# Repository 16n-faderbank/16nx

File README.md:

# 16nx: ECAD files

Electronics CAD and design for the 16nx faderbank, in KiCAD 8.0.4 format.

## Revision

Board revision C

## Design Notes

16nx is a redesign of the original [16n][16n] project. It has identical functionality to the original project. The changes are:

- replace Teensy 3.2 board with RP2040 microcontroller and supporting circuitry, directly on the board
- move to USB-C connector
- add more power filtering onto 5V line
- redesign analog circuitry for CV outs. Rather than running the faders at 5V and dividing down to ~3.2V for the microcontroller, 16nx runs at 3.3V everywhere, and amplifies fader values _up_ to ~5V via the MCP6004 opamps.
- move to vertical Thonkiconn jacks for CV outputs (cheaper, easier to access, easier to purchase)
- move to new horizontal jack parts for MIDI/I2C, ensuring there are no connectors on front panel (4332.2330 Schurter jacks)
- assume all SMT will be machine-placed; passives are now down to 0402, various QFN/USON parts that should be reflowed.

The only manual assembly anticipated on the board is of the through-hole components: faders, jacks, switch. Everything else is expected to be assembled via a PCBA house. The product is designed around relatively generic, off-the-shelf parts available at eg [JLC][jlc].

Gerbers are not committed to the repository; they will be supplied as part of releases.

## BOM

Bom is in `16nx-bom.csv`. It contains descriptions of parts and part numbers either at JLC or at Mouser, which is how the author built his boards. Thonkiconn are available from [Thonk][thonk].

In general, most of the passives requirements are not fussy: 1% resistors and capacitors with suitable voltage tolerance will be fine. The crystal and its capacitors are quite specifically chosen, as is the Winbond flash RAM.

The Alps faders are available in a number of resistances; the actual resistance of the fader doesn't matter, it's just being used as a voltage divider; if you can't get 10k but _can_ get 20k faders, that's fine. They **must** be linear taper, however. Do not use log/audio taper faders; you _cannot_ fix that in software. (Yes, people have asked.)

## Debug connector

The debug connector on the front of the board is a JST-SH connector breaking out ARM SWD (single-wire-debug) ready for connection to a [Pico Debug Probe][debugprobe]. This allows developers to use open-source debug tools (OpenOCD, [Cortex Debug](https://github.com/Marus/cortex-debug)) to debug the firmware in a more... pleasant manner than endless serial dumps.

## I2C pullups

Two 4.7kohm pullups are available for the I2C lines. To engage them, join the two solder jumpers at the top left of the board with a blob of solder. (You may not need these if you already have suitable pull-up impedance on your I2C lines).

## Pinouts

| GPIO | Description        |
| ---- | ------------------ |
| 2    | On board LED       |
| 4    | UART TX (MIDI OUT) |
| 10   | SDA (I2C1)         |
| 11   | SCL (I2C1)         |
| 18   | S0                 |
| 19   | S1                 |
| 20   | S2                 |
| 21   | S3                 |
| 26   | ADC0               |

## Front panels

Alongside the usual KiCAD files, this directory also includes a `panels` directory containing DXF files for top/bottom panels, and a mechanical drawing of the top panel. A schematic in PDF format is also included.

## Licensing

As per the `LICENSE.md` file, the 16nx hardware is licensed as **[Creative Commons Attribution-Share-Alike 4.0][ccsa]**.

---

[octobom]: https://octopart.com/bom-tool/unJxkzvR
[16n]: https://github.com/16n-faderbank/16n/tree/main/electronics
[jlc]: https://jlcpcb.com/
[ccsa]: https://creativecommons.org/licenses/by-sa/4.0/legalcode
[thonk]: https://thonk.co.uk/

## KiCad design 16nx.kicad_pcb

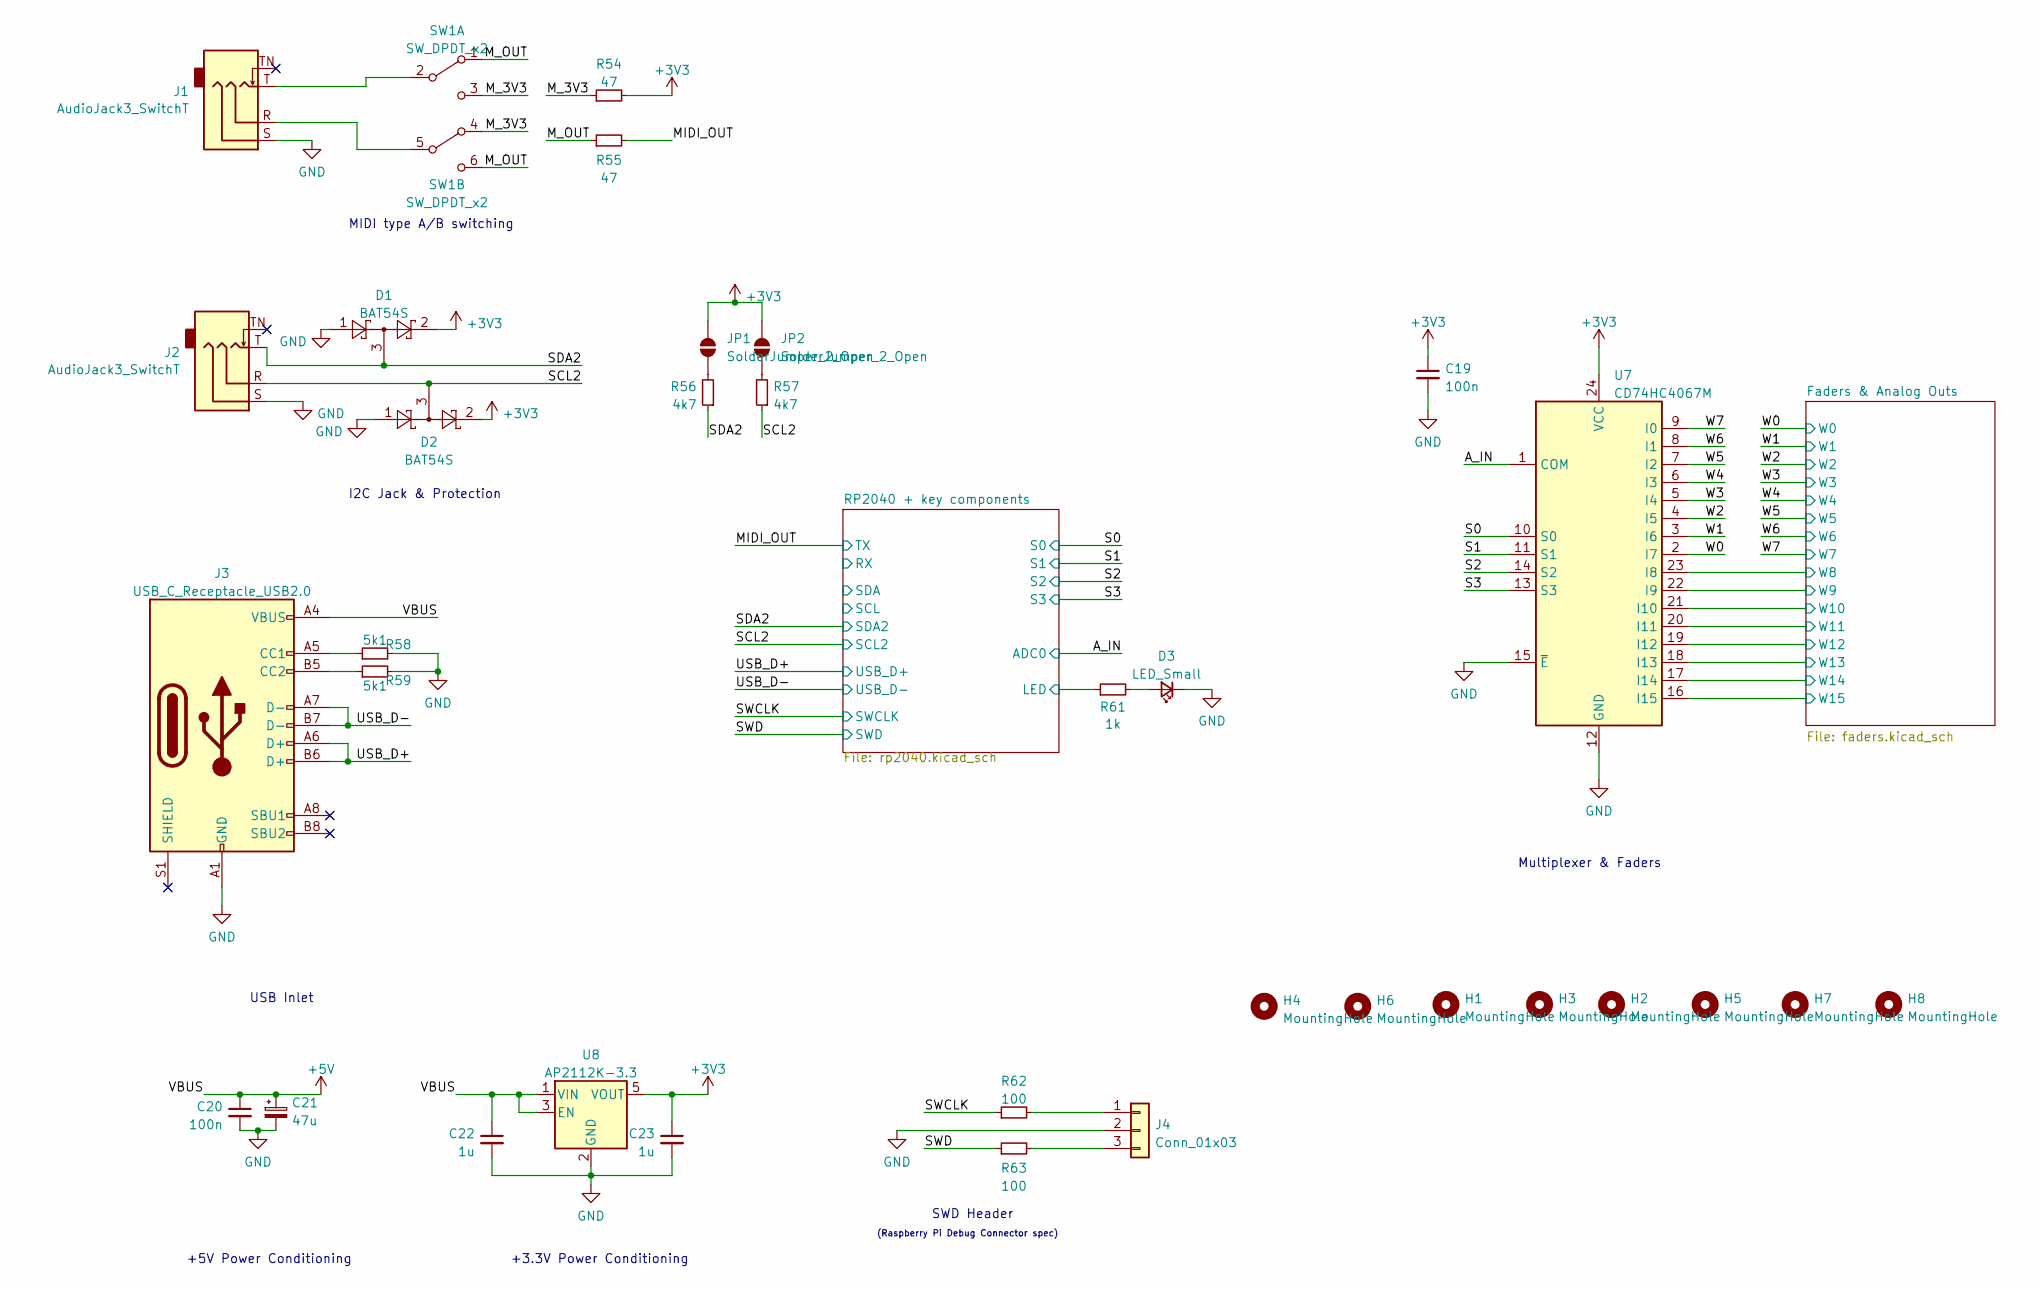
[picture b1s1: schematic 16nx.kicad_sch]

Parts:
C19, C20: 100n; C_0402_1005Metric
C21: 47u; CP_Elec_5x5.4
C22, C23: 1u; C_0402_1005Metric
D1, D2: BAT54S; SOT-23
D3: LED_Small; LED_0805_2012Metric_Pad1.15x1.40mm_HandSolder
H1, H2, H3, H4, H5, H6, H7, H8: MountingHole; MountingHole_2.7mm_M2.5
J1, J2: AudioJack3_SwitchT; Schurter 4832.2330
J3: USB_C_Receptacle_USB2.0; USB_C_Receptacle_HRO_TYPE-C-31-M-12
J4: Conn_01x03; JST_SM03B-SRSS-TB(LF)(SN)
JP1, JP2: SolderJumper_2_Open; SolderJumper-2_P1.3mm_Open_RoundedPad1.0x1.5mm
R54, R55: 47; R_0402_1005Metric
R56, R57: 4k7; R_0402_1005Metric
R58, R59: 5k1; R_0402_1005Metric
R61: 1k; R_0402_1005Metric
R62, R63: 100; R_0402_1005Metric
SW1: SW_DPDT_x2; SW_E-Switch_EG2211_DPDT
U7: CD74HC4067M; SSOP-24_5.3x8.2mm_P0.65mm
U8: AP2112K-3.3; SOT-23-5

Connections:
+3V3: C19.1, C23.1, D1.2, D2.2, JP1.2 (B), JP2.2 (B), R54.2, U7.24 (VCC), U8.5 (VOUT); also elsewhere on the board
+5V: C20.1, C21.1, C22.1, J3.A4 (VBUS), J3.A9 (VBUS), J3.B4 (VBUS), J3.B9 (VBUS), U8.1 (VIN), U8.3 (EN); also elsewhere on the board
/A_IN: U7.1 (COM); also elsewhere on the board
/Faders & Analog Outs/W8: U7.23 (I8); also elsewhere on the board
/Faders & Analog Outs/W9: U7.22 (I9); also elsewhere on the board
/Faders & Analog Outs/W10: U7.21 (I10); also elsewhere on the board
/Faders & Analog Outs/W11: U7.20 (I11); also elsewhere on the board
/Faders & Analog Outs/W12: U7.19 (I12); also elsewhere on the board
/Faders & Analog Outs/W13: U7.18 (I13); also elsewhere on the board
/Faders & Analog Outs/W14: U7.17 (I14); also elsewhere on the board
/Faders & Analog Outs/W15: U7.16 (I15); also elsewhere on the board
/MIDI_OUT: R55.2; also elsewhere on the board
/M_3V3: R54.1, SW1.3 (C), SW1.4 (A)
/M_OUT: R55.1, SW1.1 (A), SW1.6 (C)
/RP2040 + key components/LED: R61.1; also elsewhere on the board
/S0: U7.10 (S0); also elsewhere on the board
/S1: U7.11 (S1); also elsewhere on the board
/S2: U7.14 (S2); also elsewhere on the board
/S3: U7.13 (S3); also elsewhere on the board
/SCL2: D2.3, J2.R, R57.1; also elsewhere on the board
/SDA2: D1.3, J2.T, R56.1; also elsewhere on the board
/SWCLK: R62.1; also elsewhere on the board
/SWD: R63.1; also elsewhere on the board
/USB_D+: J3.A6 (D+), J3.B6 (D+); also elsewhere on the board
/USB_D-: J3.A7 (D-), J3.B7 (D-); also elsewhere on the board
/W0: U7.2 (I7); also elsewhere on the board
/W1: U7.3 (I6); also elsewhere on the board
/W2: U7.4 (I5); also elsewhere on the board
/W3: U7.5 (I4); also elsewhere on the board
/W4: U7.6 (I3); also elsewhere on the board
/W5: U7.7 (I2); also elsewhere on the board
/W6: U7.8 (I1); also elsewhere on the board
/W7: U7.9 (I0); also elsewhere on the board
GND: C19.2, C20.2, C21.2, C22.2, C23.2, D1.1, D2.1, D3.1 (K), J1.S, J2.S, J3.A1 (GND), J3.A12 (GND), J3.B1 (GND), J3.B12 (GND), J4.2, R58.2, R59.2, U7.12 (GND), U7.15 (~E), U8.2 (GND); also elsewhere on the board
unnamed: D3.2 (A), R61.2
unnamed: J3.A5 (CC1), R58.1
unnamed: J3.B5 (CC2), R59.1
unnamed: J4.1, R62.2
unnamed: J4.3, R63.2
unnamed: JP1.1 (A), R56.2
unnamed: JP2.1 (A), R57.2
unnamed: J1.T, SW1.2 (B)
unnamed: J1.R, SW1.5 (B)

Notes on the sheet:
USB Inlet
+5V Power Conditioning
I2C Jack & Protection
SWD Header
+3.3V Power Conditioning
MIDI type A/B switching
(Raspberry Pi Debug Connector spec)
Multiplexer & Faders

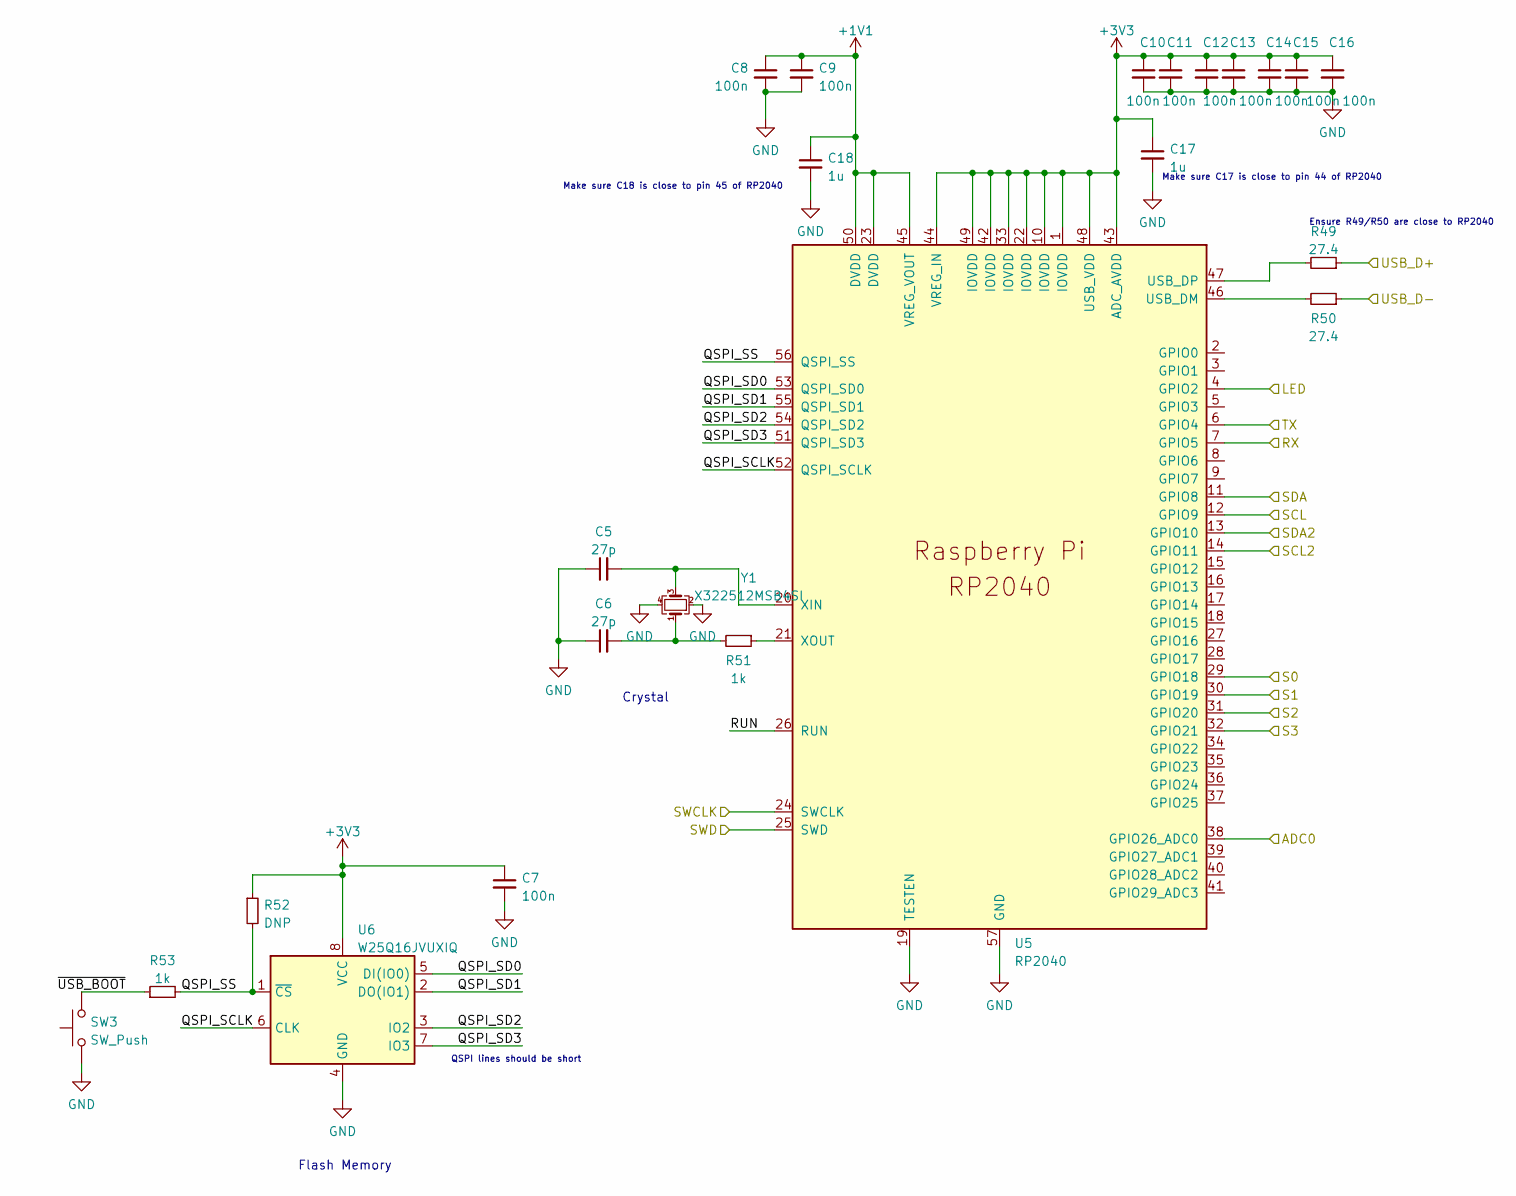
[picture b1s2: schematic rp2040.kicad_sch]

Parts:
C5, C6: 27p; C_0402_1005Metric
C7, C8, C9, C10, C11, C12, C13, C14, C15, C16: 100n; C_0402_1005Metric
C17, C18: 1u; C_0402_1005Metric
R49, R50: 27.4; R_0402_1005Metric
R51, R53: 1k; R_0402_1005Metric
R52: DNP; R_0402_1005Metric
SW3: SW_Push; SW_SPST_EVQP2
U5: RP2040; RP2040-QFN-56
U6: W25Q16JVUXIQ; USON-8_L3.0-W2.0-P0.50-BL-EP
Y1: X322512MSB4SI; Crystal_SMD_3225-4Pin_3.2x2.5mm

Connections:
+1V1: C8.1, C9.1, C18.1, U5.23 (DVDD), U5.45 (VREG_VOUT), U5.50 (DVDD)
+3V3: C7.1, C10.1, C11.1, C12.1, C13.1, C14.1, C15.1, C16.1, C17.1, R52.1, U5.1 (IOVDD), U5.10 (IOVDD), U5.22 (IOVDD), U5.33 (IOVDD), U5.42 (IOVDD), U5.43 (ADC_AVDD), U5.44 (VREG_IN), U5.48 (USB_VDD), U5.49 (IOVDD), U6.8 (VCC); also elsewhere on the board
/A_IN: U5.38 (GPIO26_ADC0); also elsewhere on the board
/MIDI_OUT: U5.6 (GPIO4); also elsewhere on the board
/RP2040 + key components/LED: U5.4 (GPIO2); also elsewhere on the board
/RP2040 + key components/QSPI_SCLK: U5.52 (QSPI_SCLK), U6.6 (CLK)
/RP2040 + key components/QSPI_SD0: U5.53 (QSPI_SD0), U6.5 (DI(IO0))
/RP2040 + key components/QSPI_SD1: U5.55 (QSPI_SD1), U6.2 (DO(IO1))
/RP2040 + key components/QSPI_SD2: U5.54 (QSPI_SD2), U6.3 (IO2)
/RP2040 + key components/QSPI_SD3: U5.51 (QSPI_SD3), U6.7 (IO3)
/RP2040 + key components/QSPI_SS: R52.2, R53.2, U5.56 (QSPI_SS), U6.1 (~CS)
/RP2040 + key components/RUN: U5.26 (RUN)
/RP2040 + key components/RX: U5.7 (GPIO5)
/RP2040 + key components/SCL: U5.12 (GPIO9)
/RP2040 + key components/SDA: U5.11 (GPIO8)
/RP2040 + key components/~USB_BOOT: R53.1, SW3.2
/S0: U5.29 (GPIO18); also elsewhere on the board
/S1: U5.30 (GPIO19); also elsewhere on the board
/S2: U5.31 (GPIO20); also elsewhere on the board
/S3: U5.32 (GPIO21); also elsewhere on the board
/SCL2: U5.14 (GPIO11); also elsewhere on the board
/SDA2: U5.13 (GPIO10); also elsewhere on the board
/SWCLK: U5.24 (SWCLK); also elsewhere on the board
/SWD: U5.25 (SWD); also elsewhere on the board
/USB_D+: R49.1; also elsewhere on the board
/USB_D-: R50.1; also elsewhere on the board
GND: C5.1, C6.1, C7.2, C8.2, C9.2, C10.2, C11.2, C12.2, C13.2, C14.2, C15.2, C16.2, C17.2, C18.2, SW3.1, U5.19 (TESTEN), U5.57 (GND), U6.4 (GND), Y1.2, Y1.4; also elsewhere on the board
unnamed: C6.2, R51.2, Y1.1
unnamed: R50.2, U5.46 (USB_DM)
unnamed: R49.2, U5.47 (USB_DP)
unnamed: C5.2, U5.20 (XIN), Y1.3
unnamed: R51.1, U5.21 (XOUT)

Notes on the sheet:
Crystal
Ensure R49/R50 are close to RP2040
Make sure C17 is close to pin 44 of RP2040
Flash Memory
QSPI lines should be short
Make sure C18 is close to pin 45 of RP2040

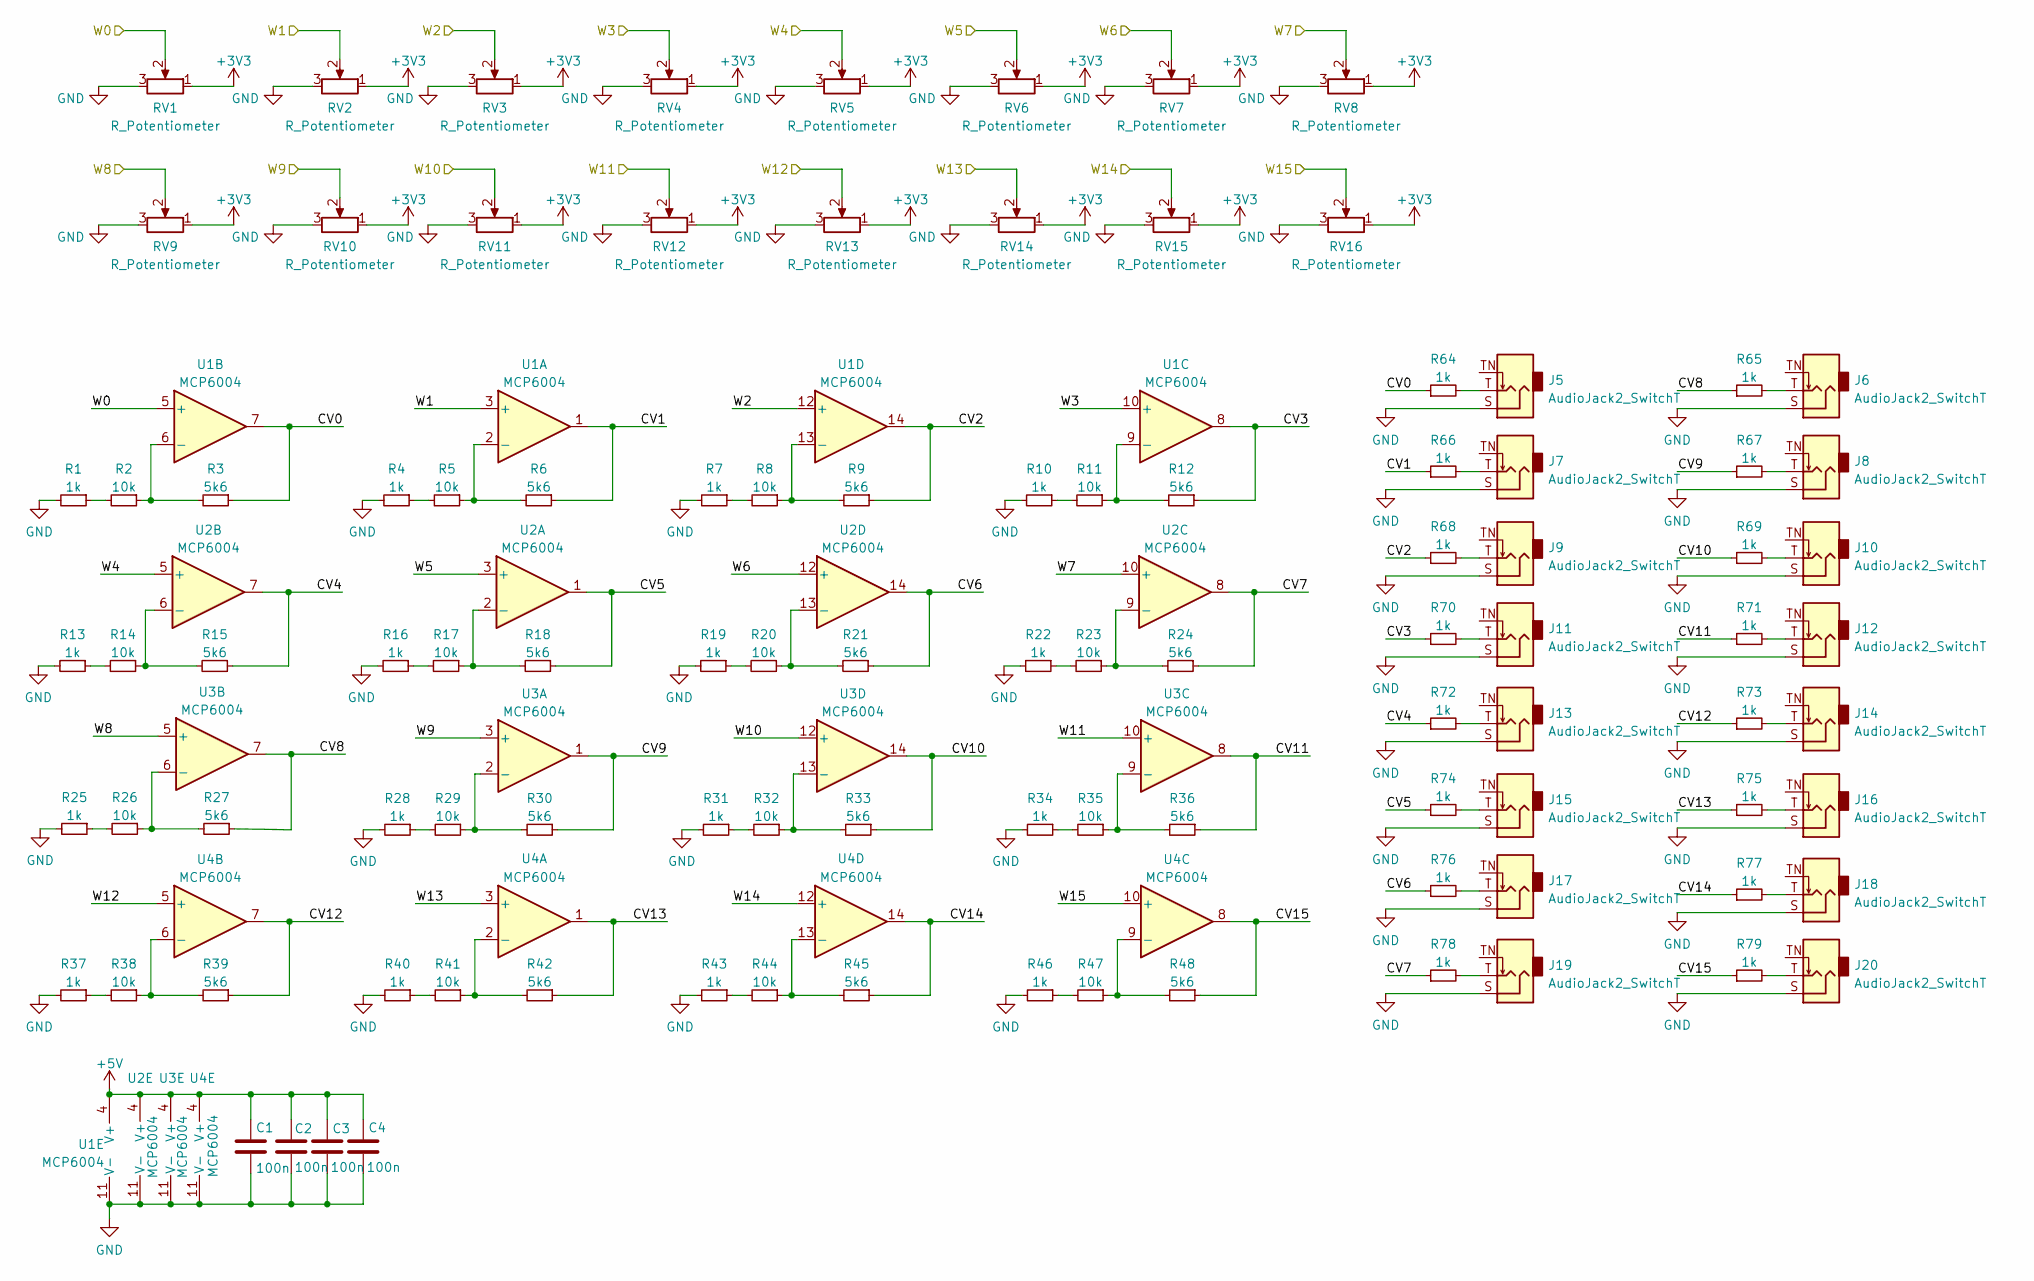
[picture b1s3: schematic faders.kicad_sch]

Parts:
C1, C2, C3, C4: 100n; C_0402_1005Metric
J5, J6, J7, J8, J9, J10, J11, J12, J13, J14, J15, J16, J17, J18, J19, J20: AudioJack2_SwitchT; Thonkiconn
R1, R4, R7, R10, R13, R16, R19, R22, R25, R28, R31, R34, R37, R40, R43, R46, R64, R65, R66, R67, R68, R69, R70, R71, R72, R73, R74, R75, R76, R77, R78, R79: 1k; R_0402_1005Metric
R2, R5, R8, R11, R14, R17, R20, R23, R26, R29, R32, R35, R38, R41, R44, R47: 10k; R_0402_1005Metric
R3, R6, R9, R12, R15, R18, R21, R24, R27, R30, R33, R36, R39, R42, R45, R48: 5k6; R_0402_1005Metric
RV1, RV2, RV3, RV4, RV5, RV6, RV7, RV8, RV9, RV10, RV11, RV12, RV13, RV14, RV15, RV16: R_Potentiometer; Alps_60mm_Fader
U1, U2, U3, U4: MCP6004; SOIC-14_3.9x8.7mm_P1.27mm

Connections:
+3V3: RV1.1, RV2.1, RV3.1, RV4.1, RV5.1, RV6.1, RV7.1, RV8.1, RV9.1, RV10.1, RV11.1, RV12.1, RV13.1, RV14.1, RV15.1, RV16.1; also elsewhere on the board
+5V: C1.1, C2.1, C3.1, C4.1, U1.4 (V+), U2.4 (V+), U3.4 (V+), U4.4 (V+); also elsewhere on the board
/Faders & Analog Outs/CV0: R3.1, R64.1, U1.7
/Faders & Analog Outs/CV1: R6.1, R66.1, U1.1
/Faders & Analog Outs/CV2: R9.1, R68.1, U1.14
/Faders & Analog Outs/CV3: R12.1, R70.1, U1.8
/Faders & Analog Outs/CV4: R15.1, R72.1, U2.7
/Faders & Analog Outs/CV5: R18.1, R74.1, U2.1
/Faders & Analog Outs/CV6: R21.1, R76.1, U2.14
/Faders & Analog Outs/CV7: R24.1, R78.1, U2.8
/Faders & Analog Outs/CV8: R27.1, R65.1, U3.7
/Faders & Analog Outs/CV9: R30.1, R67.1, U3.1
/Faders & Analog Outs/CV10: R33.1, R69.1, U3.14
/Faders & Analog Outs/CV11: R36.1, R71.1, U3.8
/Faders & Analog Outs/CV12: R39.1, R73.1, U4.7
/Faders & Analog Outs/CV13: R42.1, R75.1, U4.1
/Faders & Analog Outs/CV14: R45.1, R77.1, U4.14
/Faders & Analog Outs/CV15: R48.1, R79.1, U4.8
/Faders & Analog Outs/W8: RV9.2, U3.5 (+); also elsewhere on the board
/Faders & Analog Outs/W9: RV10.2, U3.3 (+); also elsewhere on the board
/Faders & Analog Outs/W10: RV11.2, U3.12 (+); also elsewhere on the board
/Faders & Analog Outs/W11: RV12.2, U3.10 (+); also elsewhere on the board
/Faders & Analog Outs/W12: RV13.2, U4.5 (+); also elsewhere on the board
/Faders & Analog Outs/W13: RV14.2, U4.3 (+); also elsewhere on the board
/Faders & Analog Outs/W14: RV15.2, U4.12 (+); also elsewhere on the board
/Faders & Analog Outs/W15: RV16.2, U4.10 (+); also elsewhere on the board
/W0: RV1.2, U1.5 (+); also elsewhere on the board
/W1: RV2.2, U1.3 (+); also elsewhere on the board
/W2: RV3.2, U1.12 (+); also elsewhere on the board
/W3: RV4.2, U1.10 (+); also elsewhere on the board
/W4: RV5.2, U2.5 (+); also elsewhere on the board
/W5: RV6.2, U2.3 (+); also elsewhere on the board
/W6: RV7.2, U2.12 (+); also elsewhere on the board
/W7: RV8.2, U2.10 (+); also elsewhere on the board
GND: C1.2, C2.2, C3.2, C4.2, J5.S, J6.S, J7.S, J8.S, J9.S, J10.S, J11.S, J12.S, J13.S, J14.S, J15.S, J16.S, J17.S, J18.S, J19.S, J20.S, R1.2, R4.2, R7.2, R10.2, R13.2, R16.2, R19.2, R22.2, R25.2, R28.2, R31.2, R34.2, R37.2, R40.2, R43.2, R46.2, RV1.3, RV2.3, RV3.3, RV4.3, RV5.3, RV6.3, RV7.3, RV8.3, RV9.3, RV10.3, RV11.3, RV12.3, RV13.3, RV14.3, RV15.3, RV16.3, U1.11 (V-), U2.11 (V-), U3.11 (V-), U4.11 (V-); also elsewhere on the board
unnamed: J5.T, R64.2
unnamed: J6.T, R65.2
unnamed: J7.T, R66.2
unnamed: J8.T, R67.2
unnamed: J9.T, R68.2
unnamed: J10.T, R69.2
unnamed: J11.T, R70.2
unnamed: J12.T, R71.2
unnamed: J13.T, R72.2
unnamed: J14.T, R73.2
unnamed: J15.T, R74.2
unnamed: J16.T, R75.2
unnamed: J17.T, R76.2
unnamed: J18.T, R77.2
unnamed: J19.T, R78.2
unnamed: J20.T, R79.2
unnamed: R1.1, R2.2
unnamed: R4.1, R5.2
unnamed: R7.1, R8.2
unnamed: R10.1, R11.2
unnamed: R13.1, R14.2
unnamed: R16.1, R17.2
unnamed: R19.1, R20.2
unnamed: R22.1, R23.2
unnamed: R25.1, R26.2
unnamed: R28.1, R29.2
unnamed: R31.1, R32.2
unnamed: R34.1, R35.2
unnamed: R37.1, R38.2
unnamed: R40.1, R41.2
unnamed: R43.1, R44.2
unnamed: R46.1, R47.2
unnamed: R5.1, R6.2, U1.2 (-)
unnamed: R2.1, R3.2, U1.6 (-)
unnamed: R11.1, R12.2, U1.9 (-)
unnamed: R8.1, R9.2, U1.13 (-)
unnamed: R17.1, R18.2, U2.2 (-)
unnamed: R14.1, R15.2, U2.6 (-)
unnamed: R23.1, R24.2, U2.9 (-)
unnamed: R20.1, R21.2, U2.13 (-)
unnamed: R29.1, R30.2, U3.2 (-)
unnamed: R26.1, R27.2, U3.6 (-)
unnamed: R35.1, R36.2, U3.9 (-)
unnamed: R32.1, R33.2, U3.13 (-)
unnamed: R41.1, R42.2, U4.2 (-)
unnamed: R38.1, R39.2, U4.6 (-)
unnamed: R47.1, R48.2, U4.9 (-)
unnamed: R44.1, R45.2, U4.13 (-)

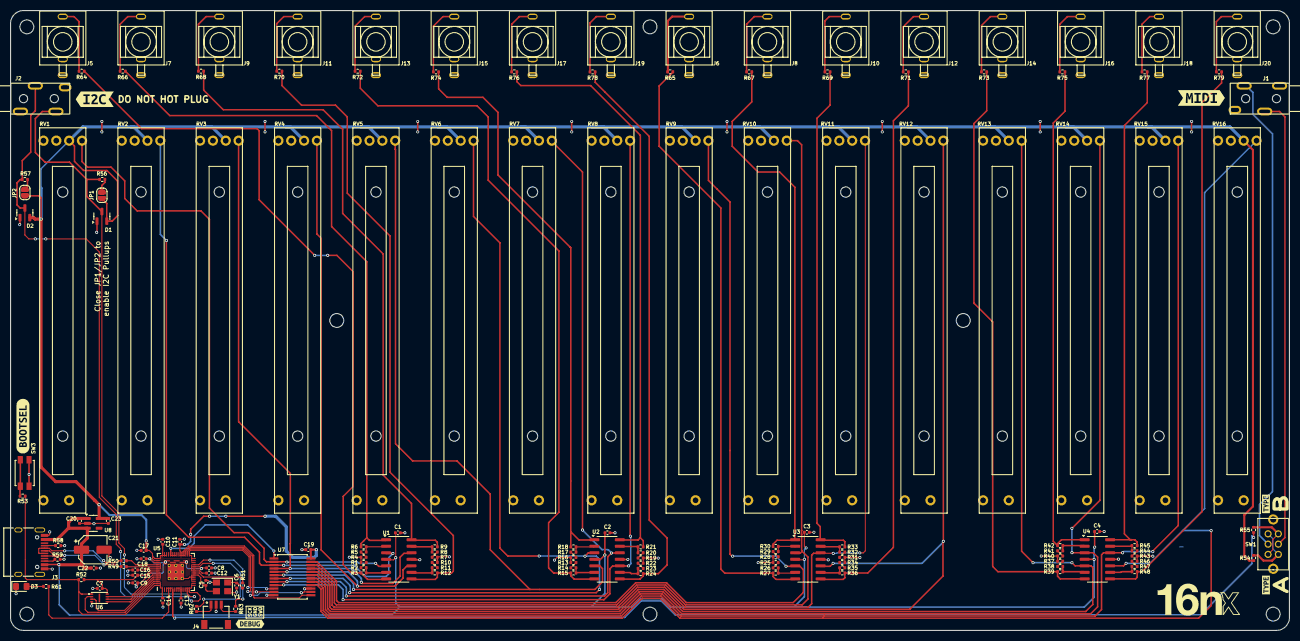
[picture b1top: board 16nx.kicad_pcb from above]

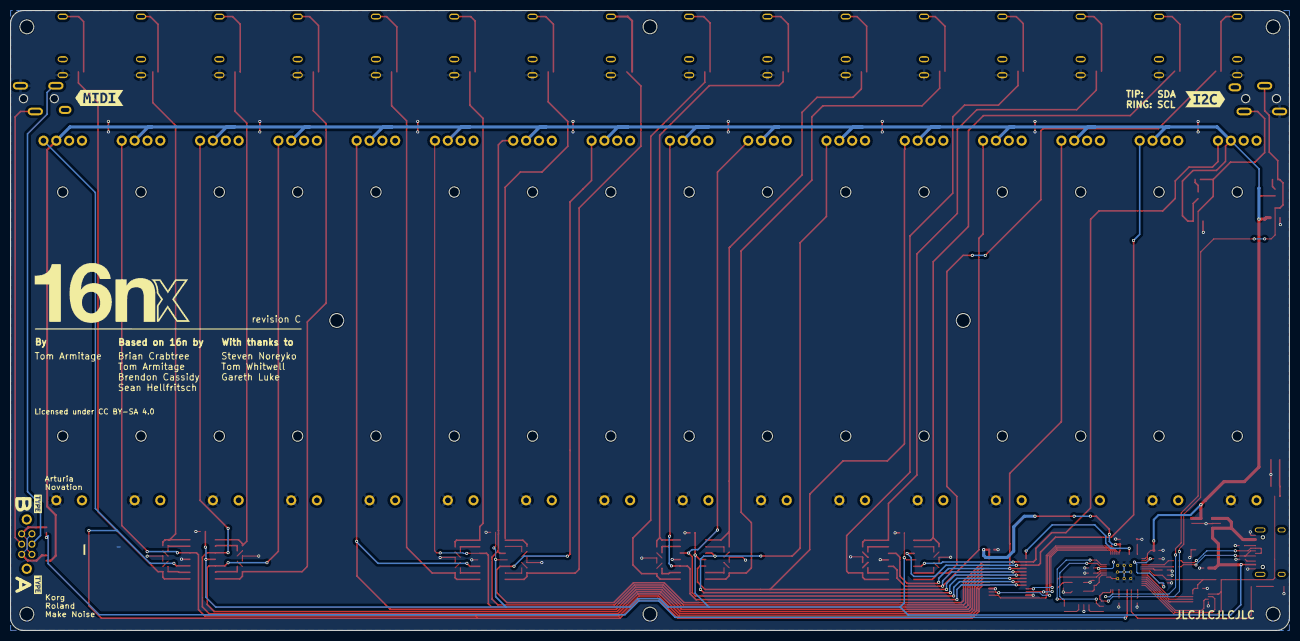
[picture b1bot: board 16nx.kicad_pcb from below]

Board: 2 copper layers, 248.9 x 120.6 mm, 171 parts (4 on the bottom side), 120 nets.

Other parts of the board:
kibuzzard-65F9938A, kibuzzard-65F9938A#2: G***; kibuzzard-65F9938A
kibuzzard-65F99372, kibuzzard-65F99372#2: G***; kibuzzard-65F99372
kibuzzard-65F99422: G***; kibuzzard-65F99422
kibuzzard-65F99486: G***; kibuzzard-65F99486
kibuzzard-66DB278F: G***; kibuzzard-66DB278F
kibuzzard-66DB2915: G***; kibuzzard-66DB2915
kibuzzard-6499C329: G***; kibuzzard-6499C329
kibuzzard-64709A08: G***; kibuzzard-64709A08

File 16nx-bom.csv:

Reference,Value,Footprint,Qty,DNP,Description,JLCPCB Part,Mouser Part
"C1,C2,C3,C4,C7,C8,C9,C10,C11,C12,C13,C14,C15,C16,C19,C20",100n,0402,16,,100nF 16V X7R 10% capacitor,C1525,
"C5,C6",27p,0402,2,,27pF 50V C0G 5% capacitor,C1557,
"C17,C18,C22,C23",1u,0402,4,,1uF 25V X7R 10% capacitor,C52923,
C21,47u,5x5.4mm capacitor,1,,47uF 16V electrolytic capacitor,C4747957,
"D1,D2",BAT54S,SOT-23,2,,series schottky diode,C916425,
D3,LED_Small,0805,1,,Red LED ,C84256,
"J1,J2",AudioJack3_SwitchT,ta_library:Schurter 4832.2330,2,,Schurter 4832.2330 Jack Socket,,693-4832.233
J3,USB_C_Receptacle_USB2.0,Connector_USB:USB_C_Receptacle_HRO_TYPE-C-31-M-12,1,,Korean Hroparts C-13-M-12 USB-C socket,C165948,
J4,Conn_01x03,ta_library:JST_SM03B-SRSS-TB(LF)(SN),1,,JST SM03B-SRSS-TB(LF)(SN),C160403,
"J5,J6,J7,J8,J9,J10,J11,J12,J13,J14,J15,J16,J17,J18,J19,J20",AudioJack2_SwitchT,ta_library:Thonkiconn,16,,Thonkiconn Jack Connector,,
"R1,R4,R7,R10,R13,R16,R19,R22,R25,R28,R31,R34,R37,R40,R43,R46,R51,R53,R61,R64,R65,R66,R67,R68,R69,R70,R71,R72,R73,R74,R75,R76,R77,R78,R79",1k,0402,35,,1kΩ 1% resistor,C11702,
"R2,R5,R8,R11,R14,R17,R20,R23,R26,R29,R32,R35,R38,R41,R44,R47",10k,0402,16,,10kΩ 1% resistor,C25744,
"R3,R6,R9,R12,R15,R18,R21,R24,R27,R30,R33,R36,R39,R42,R45,R48",5k6,0402,16,,5.6kΩ 1% resistor,C25908,
"R49,R50",27.4,0402,2,,27.4Ω 1% resistor,C284479,
R52,DNP,0402,1,,,,
"R54,R55",47,0402,2,,47Ω 1% resistor,C25118,
"R56,R57",4k7,0402,2,,4k7 1% resistor,C25900,
"R58,R59",5k1,0402,2,,5.1kΩ 1% resistor,C25905,
"R62,R63",100,0402,2,,100Ω 1% resistor,C25076,
"RV1,RV2,RV3,RV4,RV5,RV6,RV7,RV8,RV9,RV10,RV11,RV12,RV13,RV14,RV15,RV16",R_Potentiometer,ta_library:Alps_60mm_Fader,16,,Alps RS6011SP6003 fader,,688-RS6011SP6003
SW1,SW_DPDT_x2,ta_library:SW_E-Switch_EG2211_DPDT,1,,EG2211 toggle switch,,612-EG2211
SW3,SW_Push,Button_Switch_SMD:SW_SPST_EVQP2,1,,Panasonic EVQP2 3.5x4.7m SPST push switch,C79162,
"U1,U2,U3,U4",MCP6004,SOIC-14_3.9x8.7mm_P1.27mm,4,,MCP6004 opamp,C7378,
U5,RP2040,QFN56,1,,RP2040 microcontroller,C2040,
U6,W25Q16JVUXIQ,easyeda2kicad:USON-8_L3.0-W2.0-P0.50-BL-EP,1,,Winbond W25Q16JVUXIQ flash memory,C2843335,
U7,CD74HC4067M,SSOP-24_5.3x8.2mm_P0.65mm,1,,CD74HC4067 multiplexer,C98457,
U8,AP2112K-3.3,SOT-23-5,1,,3.3V LDO regulator,C3021085,
Y1,X322512MSB4SI,3225-4Pin_3.2x2.5mm,1,,12MHz SMD crystal oscillator 20pf,C9002,

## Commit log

2024-09-11 Initial commit of Revision C.
    (Previous revisions were all part of pre-release work).
2024-10-24 Update 16nx-bom.csv
    Changes CD74HC4067M -> CD74HC4067 for better likelihood that it can match the right part in assemblers like JLCPCB

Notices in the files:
16nx.kicad_pcb:
Licensed under CC BY-SA 4.0
